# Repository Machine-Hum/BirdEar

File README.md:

# BirdEar
Birdear is an open source hardware project that aims to build embedded hardware for classifying acoustic data. It uses and STM32 microcontoller, 18650 battery and a neural network build woth [Tensorflow lite for Microcontrollers](https://www.tensorflow.org/lite/microcontrollers). It is designed to be inexpensive so several units can be placed cheaply.

The training data was fetched from [xeno-canto](https://www.xeno-canto.org/)

[Report here](report/paper.pdf)

## Repo Structure
```bash
├── birdEar   # Hardware directory
├── NN        # Directory pertaining to the neural net
├── README.md # This file
├── refs      # Referance files
├── report    # Report for the project
└── src       # Source code for the firmware
```

- Jin Seo / Ryan Walker

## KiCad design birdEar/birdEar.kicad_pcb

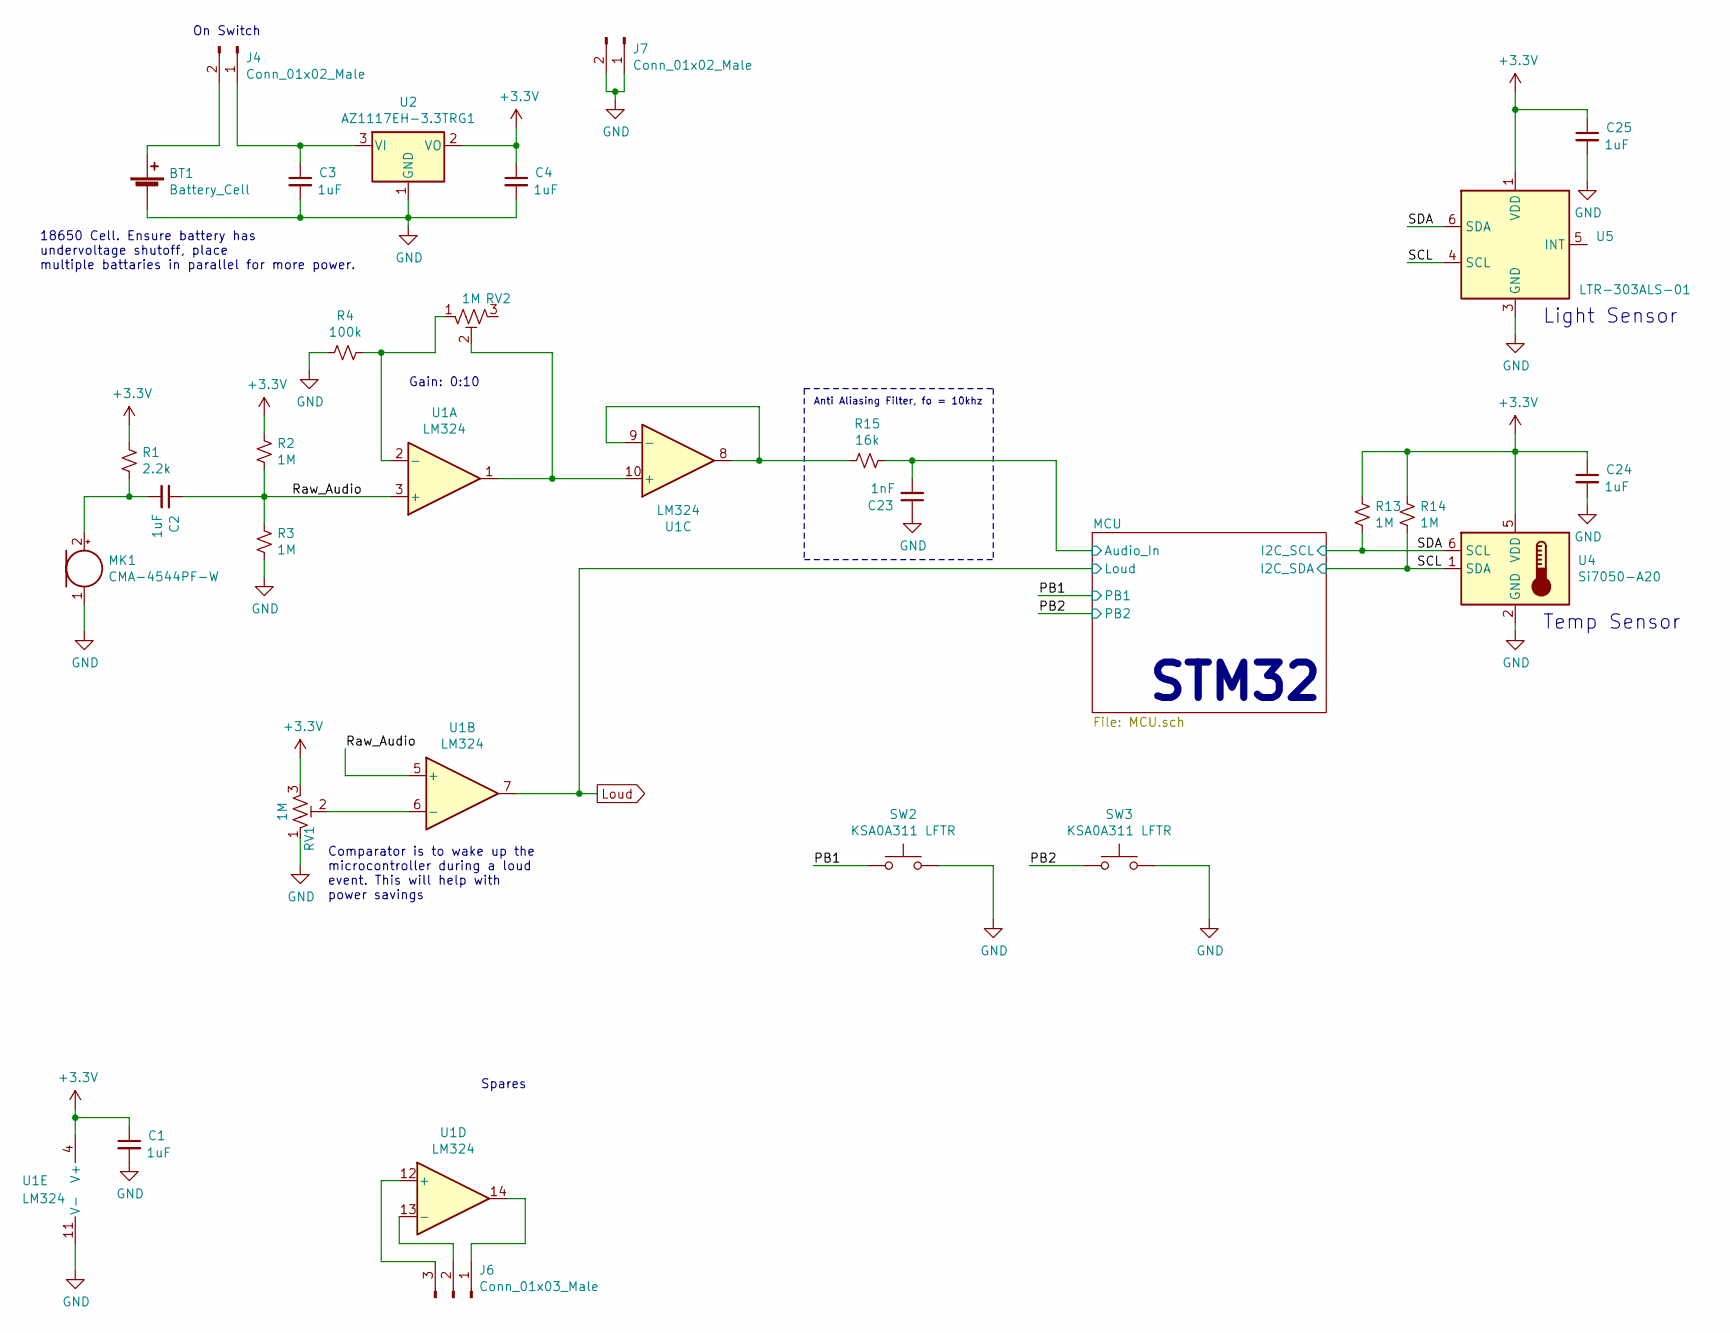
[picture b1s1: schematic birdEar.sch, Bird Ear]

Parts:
BT1: Battery_Cell; BatteryHolder_Keystone_1042_1x18650; Part Number 1042P
C1, C2, C3, C4, C24, C25: 1uF; C_0805_2012Metric
C23: 1nF; C_0805_2012Metric
J4, J7: Conn_01x02_Male; PinHeader_1x02_P2.54mm_Vertical
J6: Conn_01x03_Male; PinHeader_1x03_P2.54mm_Vertical
MK1: CMA-4544PF-W; PinHeader_1x02_P2.54mm_Vertical
R1: 2.2k; R_0805_2012Metric
R2, R3, R13, R14: 1M; R_0805_2012Metric
R4: 100k; R_0805_2012Metric
R15: 16k; R_0805_2012Metric
RV1, RV2: 1M; Potentiometer_Vishay_T73YP_Vertical; Part Number 3362P-1-105LF
SW2, SW3: KSA0A311 LFTR; SW_Tactile_Straight_KSA0Axx1LFTR
U1: LM324; SOIC-14_3.9x8.7mm_P1.27mm; Part Number LM324DR
U2: AZ1117EH-3.3TRG1; SOT-223-3_TabPin2
U4: Si7050-A20; DFN-6-1EP_3x3mm_P1mm_EP1.5x2.4mm
U5: LTR-303ALS-01; Lite-On_LTR-303ALS-01

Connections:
+3V3: C1.1, C4.1, C24.1, C25.1, R1.1, R2.1, R13.1, R14.1, RV1.3, U1.4 (V+), U2.2 (VO), U4.5 (VDD), U5.1 (VDD); also elsewhere on the board
/MCU/Audio_In: C23.2, R15.1; also elsewhere on the board
/PB1: SW2.1; also elsewhere on the board
/PB2: SW3.1; also elsewhere on the board
/Raw_Audio: C2.1, R2.2, R3.1, U1.3 (+), U1.5 (+)
/SCL: R14.2, U4.1 (SDA), U5.4 (SCL); also elsewhere on the board
/SDA: R13.2, U4.6 (SCL), U5.6 (SDA); also elsewhere on the board
GND: BT1.2 (-), C1.2, C3.2, C4.2, C23.1, C24.2, C25.2, J7.1, J7.2, MK1.1 (-), R3.2, R4.2, RV1.1, SW2.2, SW3.2, U1.11 (V-), U2.1 (GND), U4.2 (GND), U4.7, U5.3 (GND); also elsewhere on the board
Loud: U1.7; also elsewhere on the board
unnamed: BT1.1 (+), J4.2
unnamed: C2.2, MK1.2 (+), R1.2
unnamed: C3.1, J4.1, U2.3 (VI)
unnamed: J6.1, U1.14
unnamed: J6.2, U1.13 (-)
unnamed: J6.3, U1.12 (+)
unnamed: R4.1, RV2.1, U1.2 (-)
unnamed: R15.2, U1.8, U1.9 (-)
unnamed: RV1.2, U1.6 (-)
unnamed: RV2.2, U1.1, U1.10 (+)

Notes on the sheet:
18650 Cell. Ensure battery has undervoltage shutoff, place multiple battaries in parallel for more power.
Gain: 0:10
Spares
STM32
Temp Sensor
Light Sensor
On Switch
Anti Aliasing Filter, fo = 10khz
Comparator is to wake up the microcontroller during a loud event. This will help with power savings

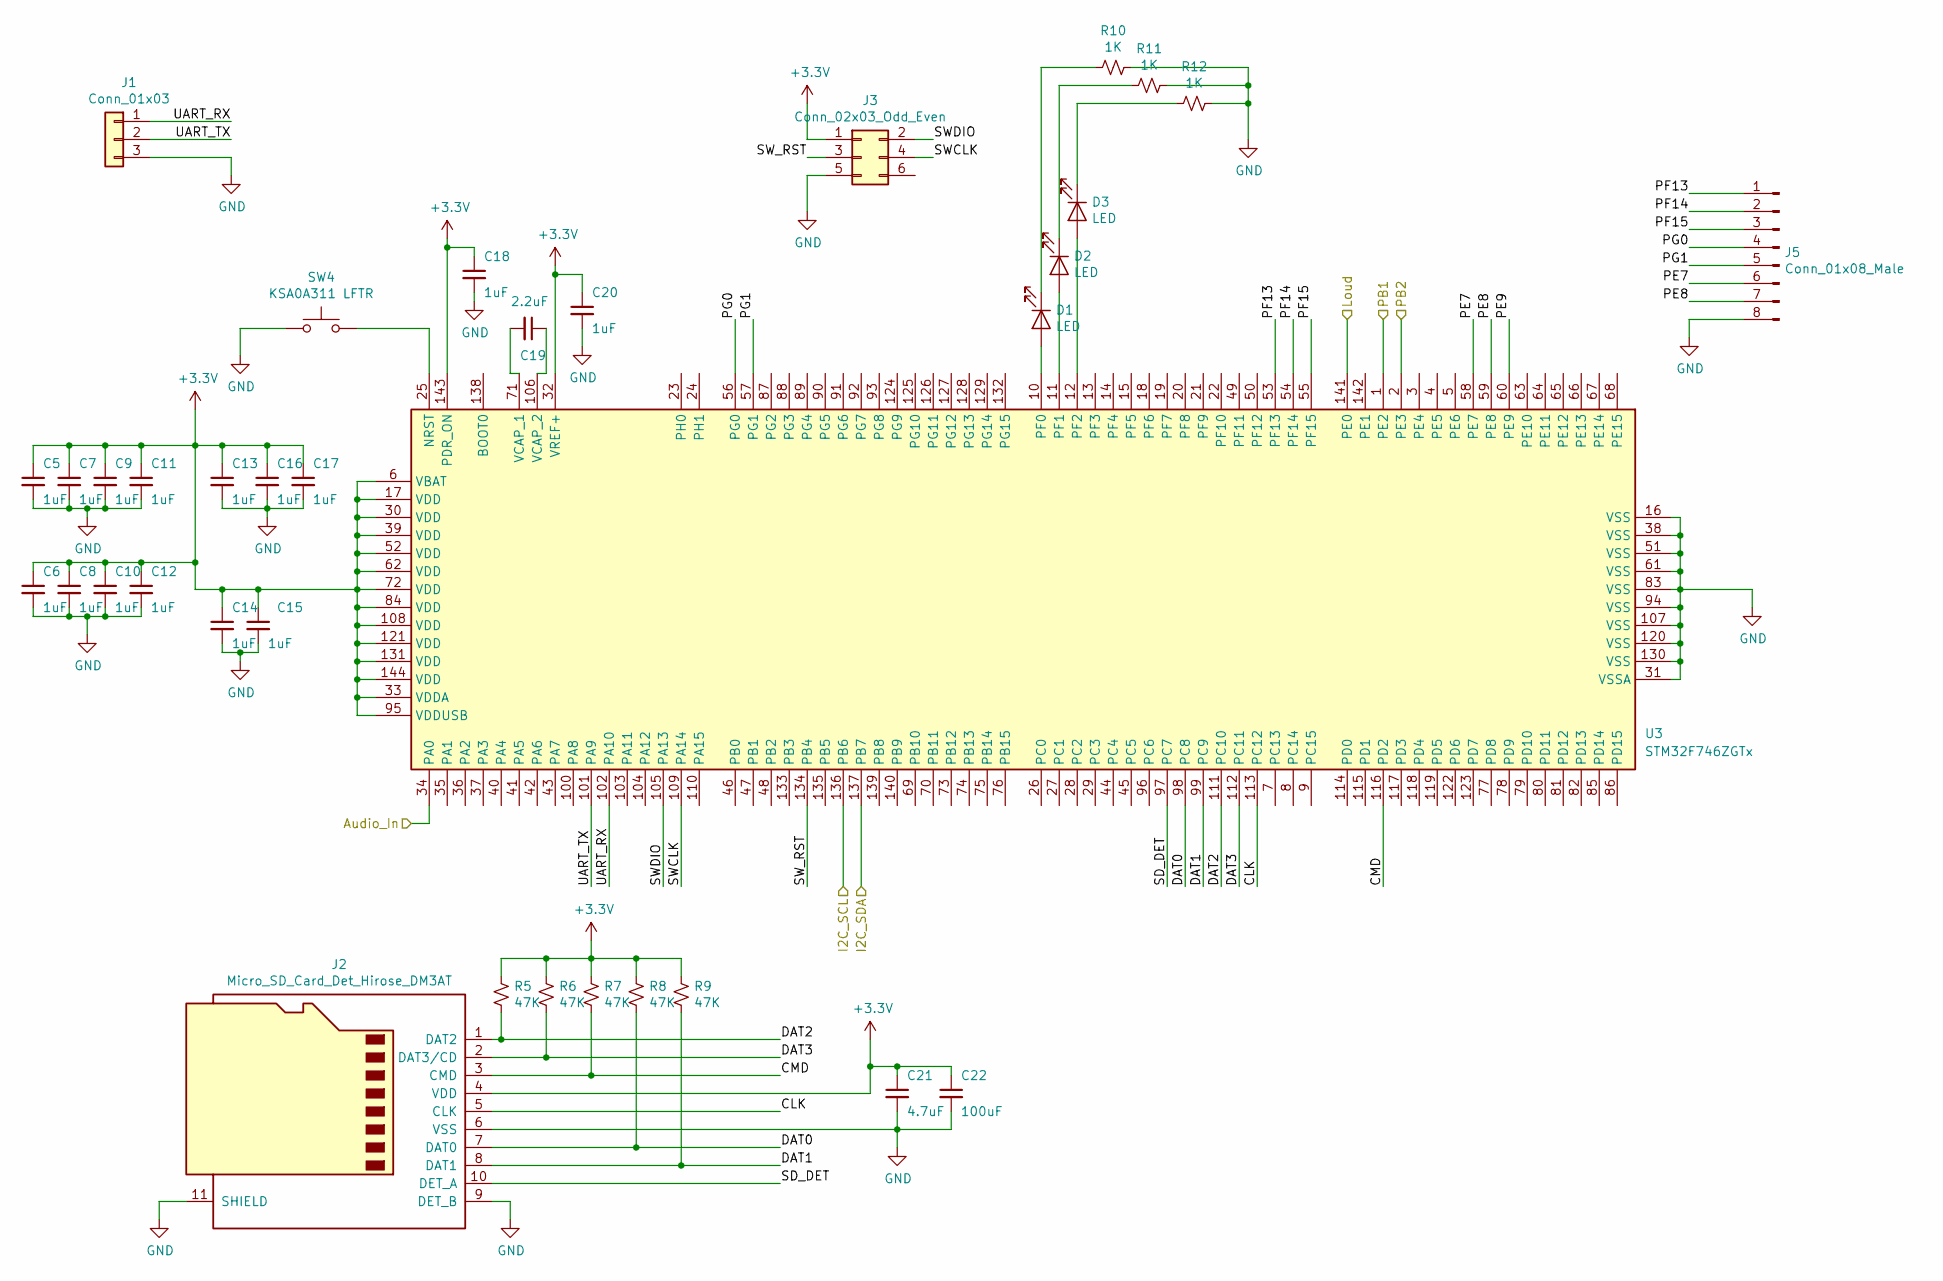
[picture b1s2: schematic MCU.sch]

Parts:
C5, C6, C7, C8, C9, C10, C11, C12, C13, C14, C15, C16, C17, C18, C20: 1uF; C_0805_2012Metric
C19: 2.2uF; C_0805_2012Metric
C21: 4.7uF; C_0805_2012Metric
C22: 100uF; C_0805_2012Metric
D1, D2, D3: LED; LED_0805_2012Metric
J1: Conn_01x03; PinHeader_1x03_P2.54mm_Vertical
J2: Micro_SD_Card_Det_Hirose_DM3AT; microSD_HC_Hirose_DM3AT-SF-PEJM5
J3: Conn_02x03_Odd_Even; PinHeader_2x03_P2.54mm_Vertical
J5: Conn_01x08_Male; PinHeader_1x08_P2.54mm_Vertical
R5, R6, R7, R8, R9: 47K; R_0805_2012Metric
R10, R11, R12: 1K; R_0805_2012Metric
SW4: KSA0A311 LFTR; SW_Tactile_Straight_KSA0Axx1LFTR
U3: STM32F746ZGTx; LQFP-144_20x20mm_P0.5mm

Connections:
+3V3: C5.1, C6.1, C7.1, C8.1, C9.1, C10.1, C11.1, C12.1, C13.1, C14.1, C15.1, C16.1, C17.1, C18.1, C20.1, C21.1, C22.1, J2.4 (VDD), J3.1, R5.1, R6.1, R7.1, R8.1, R9.1, U3.6 (VBAT), U3.17 (VDD), U3.30 (VDD), U3.32 (VREF+), U3.33 (VDDA), U3.39 (VDD), U3.52 (VDD), U3.62 (VDD), U3.72 (VDD), U3.84 (VDD), U3.95 (VDDUSB), U3.108 (VDD), U3.121 (VDD), U3.131 (VDD), U3.143 (PDR_ON), U3.144 (VDD); also elsewhere on the board
/MCU/Audio_In: U3.34 (PA0); also elsewhere on the board
/MCU/CLK: J2.5 (CLK), U3.113 (PC12)
/MCU/CMD: J2.3 (CMD), R7.2, U3.116 (PD2)
/MCU/DAT0: J2.7 (DAT0), R8.2, U3.98 (PC8)
/MCU/DAT1: J2.8 (DAT1), R9.2, U3.99 (PC9)
/MCU/DAT2: J2.1 (DAT2), R5.2, U3.111 (PC10)
/MCU/DAT3: J2.2 (DAT3/CD), R6.2, U3.112 (PC11)
/MCU/PE7: J5.6, U3.58 (PE7)
/MCU/PE8: J5.7, U3.59 (PE8)
/MCU/PE9: U3.60 (PE9)
/MCU/PF13: J5.1, U3.53 (PF13)
/MCU/PF14: J5.2, U3.54 (PF14)
/MCU/PF15: J5.3, U3.55 (PF15)
/MCU/PG0: J5.4, U3.56 (PG0)
/MCU/PG1: J5.5, U3.57 (PG1)
/MCU/SD_DET: J2.10 (DET_A), U3.97 (PC7)
/MCU/SWCLK: J3.4, U3.109 (PA14)
/MCU/SWDIO: J3.2, U3.105 (PA13)
/MCU/SW_RST: J3.3, U3.134 (PB4)
/MCU/UART_RX: J1.1, U3.102 (PA10)
/MCU/UART_TX: J1.2, U3.101 (PA9)
/PB1: U3.1 (PE2); also elsewhere on the board
/PB2: U3.2 (PE3); also elsewhere on the board
/SCL: U3.137 (PB7); also elsewhere on the board
/SDA: U3.136 (PB6); also elsewhere on the board
GND: C5.2, C6.2, C7.2, C8.2, C9.2, C10.2, C11.2, C12.2, C13.2, C14.2, C15.2, C16.2, C17.2, C18.2, C20.2, C21.2, C22.2, J1.3, J2.6 (VSS), J2.9 (DET_B), J2.11 (SHIELD), J3.5, J5.8, R10.1, R11.1, R12.1, SW4.1, U3.16 (VSS), U3.31 (VSSA), U3.38 (VSS), U3.51 (VSS), U3.61 (VSS), U3.83 (VSS), U3.94 (VSS), U3.107 (VSS), U3.120 (VSS), U3.130 (VSS); also elsewhere on the board
Loud: U3.141 (PE0); also elsewhere on the board
unnamed: C19.1, U3.106 (VCAP_2)
unnamed: C19.2, U3.71 (VCAP_1)
unnamed: D1.1 (K), R10.2
unnamed: D1.2 (A), U3.10 (PF0)
unnamed: D2.1 (K), R11.2
unnamed: D2.2 (A), U3.11 (PF1)
unnamed: D3.1 (K), R12.2
unnamed: D3.2 (A), U3.12 (PF2)
unnamed: SW4.2, U3.25 (NRST)

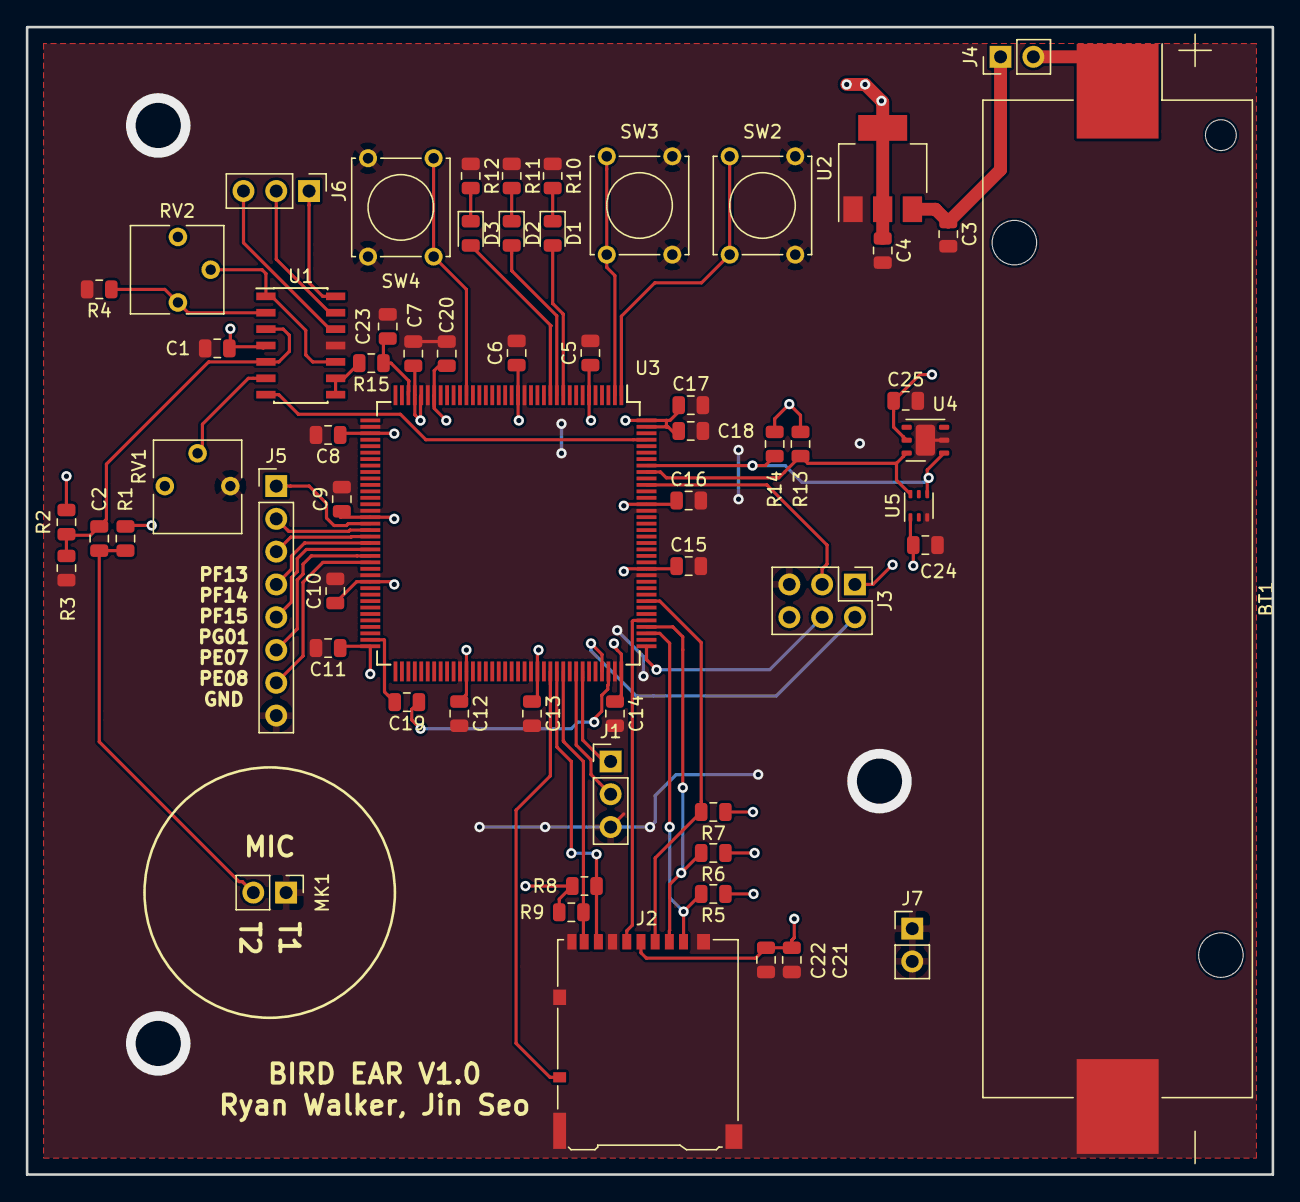
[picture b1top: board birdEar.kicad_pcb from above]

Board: 2 copper layers, 96.5 x 88.9 mm, 62 parts (0 on the bottom side), 47 nets.

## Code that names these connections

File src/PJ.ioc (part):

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Mcu.Name=STM32F746ZGTx
Mcu.Package=LQFP144
Mcu.UserName=STM32F746ZGTx
PA0/WKUP.Signal=ADCx_IN0
PA10.Signal=USART1_RX
PA9.Signal=USART1_TX
PB0.GPIOParameters=GPIO_Label
PB0.GPIO_Label=LED1
PB0.Signal=GPIO_Output
PB6.Mode=I2C
PB6.Signal=I2C1_SCL
PB7.Mode=I2C
PB7.Signal=I2C1_SDA
PC10.Mode=SD_4_bits_Wide_bus
PC10.Signal=SDMMC1_D2
PC11.Mode=SD_4_bits_Wide_bus
PC11.Signal=SDMMC1_D3
PC12.Mode=SD_4_bits_Wide_bus
PC12.Signal=SDMMC1_CK
PC7.GPIOParameters=GPIO_Label
PC7.GPIO_Label=SD_DET
PC7.Signal=GPIO_Input
PC8.Mode=SD_4_bits_Wide_bus
PC8.Signal=SDMMC1_D0
PC9.Mode=SD_4_bits_Wide_bus
PC9.Signal=SDMMC1_D1
PD2.Mode=SD_4_bits_Wide_bus
PD2.Signal=SDMMC1_CMD
PE0.GPIOParameters=GPIO_Label
PE0.GPIO_Label=Wakeup (EXTI0)
PE0.Signal=GPXTI0
PE1.GPIOParameters=GPIO_Label
PE1.GPIO_Label=PB1 (EXTI1)
PE1.Signal=GPXTI1
PE2.GPIOParameters=GPIO_Label
PE2.GPIO_Label=PB2(EXTI2)
PE2.Signal=GPXTI2
RCC.HSE_VALUE=8000000
RCC.SYSCLKFreq_VALUE=200000000
RCC.SYSCLKSource=RCC_SYSCLKSOURCE_PLLCLK
RCC.SYSCLKSourceVirtual=RCC_SYSCLKSOURCE_PLLCLK
board=NUCLEO-F746ZG
boardIOC=true

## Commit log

2019-04-30 Worked on the paper
2019-06-22 Worked on the writeup
2019-06-27 Jin's proposal
    I just add what I thought, so feel free to discuss if it doesn't go along with the project
2019-06-27 Add files via upload
    Add difficulty
2019-06-28 Moved jin's file into main document. Added some extra fields.
2019-07-03 Added some info about mel spaced filter banks.
2019-07-07 I've updated the paper
2019-07-08 Added eps files
2019-07-08 Update layout and reference
2019-07-23 Jin's commit
2019-07-23 built the pdf
2019-09-24 Added link to an SD card holder
2019-09-26 Added hardware files
2019-09-28 Create STM32Cube
2019-09-28 Add files via upload
    1. Add ports of SD card on STM32Cube
    2. Add ADC1_IN0_MiC on STM32Cube
2019-09-28 STM32Cube
    1. Add SD port to STM32Cube
    2. Add ADC1_IN0_MIC
2019-10-04 Moved some files around.
2019-10-04 Worked on the HW and made some changes to the IOC file.
2019-10-04 Changed the README
2019-10-05 Added some parts to the schematic, maps some parts to their footprints. You know.
2019-10-07 Hardware is almost finished
2019-10-07 Changes to the README
2019-10-10 Implemented anti aliasing filter, worked on the layout, added some gnd points
2019-10-12 V1.0 of the PCB Complete
2019-10-12 Generated BOM
2019-10-24 added sty file
2019-10-31 NN codes
2019-11-02 Removed submodule
2019-11-02 Codes from NN book
2019-11-02 Removed sub again
2019-11-02 Added git submodules
2019-11-02 added pdf
2019-11-03 Added a audio NN example.
2019-11-04 Added NN stuff
2019-11-04 Moved everthing to tf.keras over just keras
2019-11-04 Changed layers and now the tflite_model is generated.
2019-11-04 Fixed up the init script
2019-11-06 Created a fetcher script
2019-11-09 add codes for training and testing binary categorizing NN
2019-11-09 Modify Early Stopping verbose
2019-11-10 Chage from LSTM to SimpleRNN for Bidirectional
2019-11-11 Working on the fetcher
2019-11-11 Data organised and ready for the NN
2019-11-11 train model for tensorflow lite
2019-11-12 Added the dataset and all the other files to do with data.
2019-11-13 Modify elements of JSON
2019-11-14 Got the
2019-11-15 Data yo
2019-11-15 Serious re-org
2019-11-15 Another big re-org
2019-11-15 Still working on it
2019-11-15 Folder rename
2019-11-15 Added on biggo json file
2019-11-15 Got the nn working with the sandpiper data
2019-11-17 Worked on the paper.
2019-11-20 stft and mel
2019-11-20 Short Time Fourier Transform and Mel(MFCC and MFSC)
    Test file : stft_mel.py
    Reference codes: https://github.com/jameslyons/python_speech_features
    Clone all codes
    or just get necessary files(base.py and sigproc.py)
    Optional: create new conda environment
    For down sampling :
2019-11-20 Short Time Fourier Transform and Mel(MFCC and MFSC)
    Test file : stft_mel.py
    Reference sites:
    haythamfayek.com/2016/04/21/speech-processing-for-machine-learning.html
    http://practicalcryptography.com/miscellaneous/machine-learning/guide-mel-frequency-cepstral-coefficients-mfccs/
    Reference codes: https://github.com/jameslyons/python_speech_features
    Clone all codes
2019-11-20 Remove duplicated directory
2019-11-24 Removed libraries that can be installed with pip. Got the nn working with mel data
2019-11-27 Get out of the lib called , python_speech_features.
    Simplify functions based on our needs.
    Downsize the output dimensions by reducing the number of cepstral and window stride
    stft_mel.py is made of based on the following reference :
    https://haythamfayek.com/2016/04/21/speech-processing-for-machine-learning.html
    Sampling rate is 16 kHz which is supported by:
    https://web.wpi.edu/Pubs/E-project/Available/E-project-042910-001603/unrestricted/Bird_Call_Identification_MQP_2010.pdf
2019-11-27 Update test_mfcc.py
    correct typo
2019-11-27 correct typo
2019-11-30 Added in the firmware files
2019-12-06 Added some images
2019-12-07 Added the deck
2019-12-10 still work on latex
2019-12-10 add NN on latex
2019-12-10 add some of NN on paper
2019-12-10 add part of NN on paper
2019-12-10 remove images and move them to img folder
2019-12-10 Added BCIT logo and changed the formatting
2019-12-11 add NN on paper
2019-12-12 Complete NN and Conclusion, Appendix, etc on paper
2020-05-14 Worked on the readme
